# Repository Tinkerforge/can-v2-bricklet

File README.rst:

CAN Bricklet 2.0
================

This repository contains the firmware source code and the hardware design
files. The documentation generator configs can be found at
https://github.com/Tinkerforge/generators

Repository Content
------------------

software/:
 * examples/: Examples for all supported languages
 * build/: Compiled files
 * src/: Source code of firmware
 * Makefile: Makefile to build project

hardware/:
 * Contains KiCad project files and additionally schematics as PDF

datasheets/:
 * Contains datasheets for sensors and complex ICs that are used

Hardware
--------

The hardware is designed with the open source EDA Suite KiCad
(http://www.kicad.org). Before you are able to open the files,
you have to install the Tinkerforge kicad-libraries
(https://github.com/Tinkerforge/kicad-libraries). You can either clone
them directly in hardware/ or clone them in a separate folder and
symlink them into hardware/
(ln -s kicad_path/kicad-libraries project_path/hardware). After that you
can open the .pro file in hardware/ with KiCad and from there view and
modify the schematics and the PCB layout.

Software
--------

If you want to do your own Brick/Bricklet firmware development we highly
recommend that you use our build environment setup script and read the
tutorial (https://www.tinkerforge.com/en/doc/Tutorials/Tutorial_Build_Environment/Tutorial.html).

To compile the C code we recommend you to install the newest GNU Arm Embedded
Toolchain (https://launchpad.net/gcc-arm-embedded/+download).
You also need to install bricklib2 (https://github.com/Tinkerforge/bricklib2).

You can either clone it directly in software/src/ or clone it in a
separate folder and symlink it into software/src/
(ln -s bricklib_path/bricklib2 project_path/software/src/). Finally make sure to
have CMake installed (http://www.cmake.org/cmake/resources/software.html).

After that you can build the firmware by invoking make in software/.
The firmware (.zbin) can then be found in software/build/ and uploaded
with brickv (click button "Flashing" on start screen).

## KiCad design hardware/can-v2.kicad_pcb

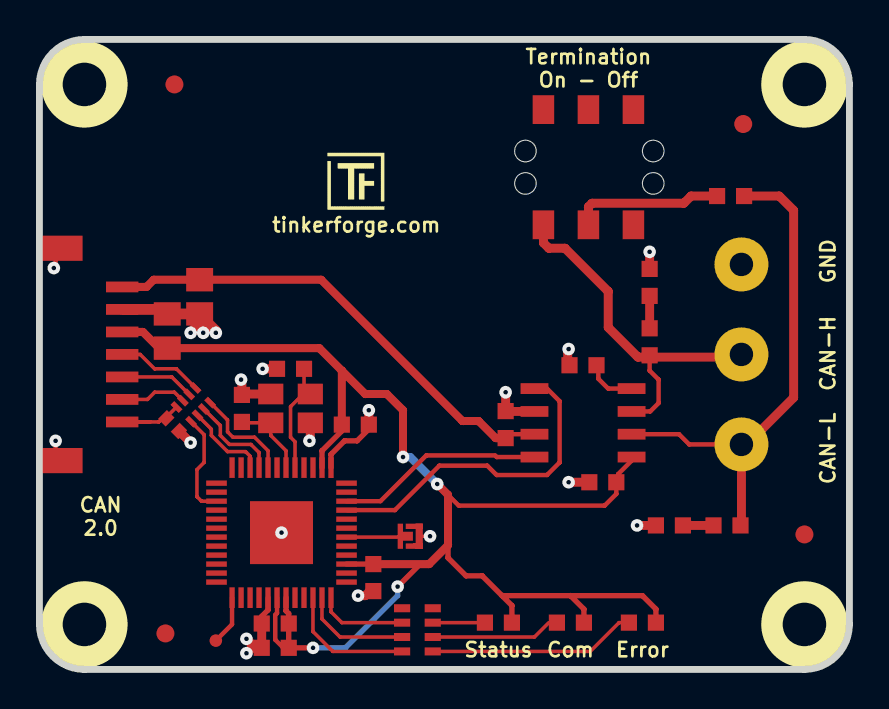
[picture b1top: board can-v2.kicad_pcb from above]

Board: 2 copper layers, 45.0 x 35.0 mm, 40 parts (0 on the bottom side), 29 nets.

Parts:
C1: 220pF; C0402F
C2, C3: 10uF; C0805E
C6, C7: 10pF; C0603F
C8, C9, C10, C12, C13: 100nF; C0603F
C11: 220nF; C0603F
C14, C15: 470pF; C0603F
D1: blue; D0603F
D2: yellow; D0603F
D3: red; D0603F
Fiducial_Mark: VAL**; Fiducial_Mark
Fiducial_Mark#2, Fiducial_Mark#3, Fiducial_Mark#4: VAL**; Fiducial_Mark
K1: CONN_3; AKL_5_3
P1: CON-SENSOR; CON-SENSOR2
P2: Debug; DEBUG_PAD
P3: Boot; SolderJumper
R2: 1k; R0603F
R3, R4, R5: 120; R0603F
RP1: 82; 4X0402
RP2: 1k; 0603X4
SW1: Termination; SLIDE_SWITCH
U1: XMC1404; QFN48-EP2
U2: MCP2562; SOIC8
U3, U4, U5, U6: DRILL; DRILL_NP
VAL: WEEE_7mm
VAL#2: CE_5mm
X1: 16MHz; CRYSTAL_3225

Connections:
3V3: C3.2, C8.2, C9.2, C10.2, C11.2, C12.1, D1.1, D2.1, D3.1, P1.3, U1.18, U1.19, U1.27, U1.38, U2.5
+5V: C2.2, C13.1, P1.1, U2.3
GND: C1.1, C2.1, C3.1, C6.2, C7.2, C8.1, C9.1, C10.1, C11.1, C12.2, C13.2, C14.2, C15.2, K1.1, P1.2, P1.EP, P3.1, R2.1, U1.17, U1.37, U1.EP, U2.2, X1.3
unnamed: C1.2, P1.7, RP1.4
unnamed: C6.1, U1.41, X1.1
unnamed: C7.1, U1.42, X1.2
unnamed: C14.1, R3.1
unnamed: C15.1, R4.1
unnamed: D1.2, RP2.7
unnamed: D2.2, RP2.6
unnamed: D3.2, RP2.5
unnamed: K1.2, R4.2, SW1.1, U2.7
unnamed: K1.3, R3.2, R5.1, U2.6
unnamed: P1.4, RP1.1
unnamed: P1.5, RP1.2
unnamed: P1.6, RP1.3
unnamed: P2.1, U1.13
unnamed: P3.2, U1.30
unnamed: R2.2, U2.8
unnamed: R5.2, SW1.2
unnamed: RP2.2, U1.24
unnamed: RP2.3, U1.23
unnamed: RP2.4, U1.22
RX: U1.34, U2.4
S-CLK: RP1.7, U1.45
S-CS: RP1.8, U1.44
S-MISO: RP1.5, U1.3
S-MOSI: RP1.6, U1.46
TX: U1.33, U2.1

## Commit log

2018-01-15 add readme
2018-01-16 add prototype hardware
2018-01-19 change text orientation
2018-02-20 Add .gitignore
2018-02-20 Cleanup KiCad libraries config
    Ensure LibDir=kicad-libraries and LibName1=tinkerforge.
    Remove special library.
2018-03-02 Add initial firmware
    That every seconds sends a dummy data frame.
2018-03-06 Add TX hardware FIFO logic
    Just transmits dummy data for now.
2018-03-06 Add MultiCAN+ datasheet
2018-03-07 Add TX buffer and feed TX FIFO from it
2018-03-07 Add custom MO helpers to avoid quirks and memory overhead in the XMC library
2018-03-07 Add RX FIFO and buffer
2018-03-08 Add basic config for extra LEDs
2018-03-08 Add simple read/write tests
2018-03-08 Rename buffer to backlog
2018-03-08 Unify count/size to size
2018-03-08 Extend write-frame to handle remote frames
2018-03-08 Split RX FIFO into multiple RX FIFOs
    To allow reception of data and remote frames along with the ability
    to have multiple acceptance filters, one per RX FIFO.
2018-03-08 Convert write/read-frame functions to streaming
2018-03-08 Add custom baudrate to bit-timing calculation
    The XMC library function for this doesn't take the DIV8 option into
    account and therefore cannot handle baudrates below 100 kbps.
2018-03-09 Fix TSEG1 range
2018-03-09 Add loopback mode using the second CAN node
2018-03-09 Fix typo in comment
2018-03-09 Whitespace
2018-03-12 Add write-buffer-timeout
2018-03-12 Add extra MO type to use last backlog slots
2018-03-12 Use frame-counter to read RF FIFOs in frame reception order
2018-03-12 Cleanup MO/buffer naming
2018-03-13 Update API
2018-03-13 Add frame-read callback
2018-03-13 Add get/set-tranceiver-configuration logic
2018-03-14 Remove unnecessary intermediate config variables
2018-03-14 Add queue and read filter configuration
2018-03-14 Add read-only mode
2018-03-14 Add communication and error LED config
2018-03-15 fix led text
2018-03-15 fix text, change logo orientation
2018-03-15 Properly handle disabled TX/RX backlogs
2018-03-15 Add error counters
2018-03-15 Reconfigure queues when entering/leaving loopback mode
    Otherwise the RX queue ends up being on the wrong CAN node, because in
    loopback the second CAN node is used for reception, but in non-loopback
    mode the first CAN node is used for transmission and reception.
2018-03-15 Don't set RXEN on RX FIFO slave objects
    This is not necessary for proper RX FIFO operation and it results in
    possible reception of frames in the middle of the RX FIFO because
    RX FIFO slave objects are normal message objects that take part in
    the acceptance filtering process if RXEN is set.
    This is especially noticable when using a read filter, because then
    frames that would be rejected by the read filter are recevied into
2018-03-15 Rename some error related things
2018-03-16 Properly recover from bus-off state
2018-03-27 specify processor
2018-04-23 Add 3d information (final)
2018-04-23 Add 3d model (*.FCStd & *.step)
2018-05-04 Rename files
2018-05-04 Add schematic PDF
2018-05-30 Add sample-point config option
2018-05-30 Add example skeletons
2018-05-30 Fix examples
2018-06-04 Disable debug
2018-06-05 examples: Fix write-frame call
2018-06-05 examples: Avoid temporary variables if possible
2018-06-05 Correctly set DIV8 config bit
2018-06-05 Add LabVIEW example
2018-06-07 Update changelog for initial release
2018-06-08 fix termination text
2018-06-18 Change capacitor footprint(s) to C0402F
2018-06-28 Fix readme
2018-07-11 Add Makefile with docker support
2018-07-11 Remove obsolete generate_makefile scripts
2018-07-11 Update directory structure and build instructions
2018-07-17 examples: Pass data as anonymous array
2018-10-04 Increase version for new release (changes in bricklib2)
2018-10-04 Add rev to changelog
2018-11-06 Add rust examples
2018-11-07 rust: Accept host names for ip connection, fix naming inconsistencies
2018-11-07 rust: Rename callback receivers.
2018-12-14 Add go examples.
2018-12-18 go: Change import path.
2018-12-18 go: Change import path again.
2018-12-20 rust: Reformat examples.
2019-01-24 mqtt: Add examples.
2019-01-24 mqtt: Remove executable bit in example permissions.
2019-01-24 go: Minor example fixes.
2019-08-22 c: Adapt to bindings changes
2019-10-04 Add initial support for timestamped frame handling
2019-11-13 Add datasheets
2020-01-14 examples: Use python3 input by default.
2020-02-26 Disable incomplete timestamped frame functions for now.
2020-02-27 Add frame readable callback.
2020-02-27 Fix disabled callback list.
2020-02-27 Mark error counters used in interrupt volatile.
2020-02-27 Add error occured callback.
2020-02-28 Fix typo.
2020-02-28 Append to changelog.
2020-02-28 Add commit ref to changelog.
2020-02-28 Fix bit0 error handling in bus-off mode
2020-02-28 Add commit ref to changelog
2020-03-16 rust: Update to new skeleton
2020-03-17 examples: Add constant translation for frame type
2020-03-17 mqtt: Fix syntax error
2020-03-17 matlab: Fix format strings
2020-03-17 vbnet: Use common style
2020-04-03 Add openHAB examples.
2020-08-19 Add uc examples.
2020-08-25 uc: Adapt example to new skeleton
2020-08-27 uc: Fix warnings.
2020-08-31 uc: Use fixed-with placeholders in format strings.
2020-09-02 uc: Add example driver note.
2020-10-27 perl: Fix syntax error
2021-05-27 php: Remove incomplete marker
2021-10-25 Update KiCad link
    https://www.kicad.org/blog/2021/10/Avoid-links-to-former-kicad-domain/
2022-04-19 examples: uc: Rename TF_HalContext to TF_HAL.
2022-04-26 uc: Adapt to bindings changes
2022-07-06 Add license files.
2022-11-09 labview: Fix SetTransceiverConfigurarion call
2022-11-10 labview: Add separate read and write examples
2022-11-14 labview: Add example for frame-read function
2025-10-04 Fix compatibility with new Docker build image (GCC 14.2.1)

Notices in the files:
hardware/can-v2.kicad_pcb:
Licensed under CERN OHL v.1.1
Copyright (©) 2018, B.Nordmeyer
Copyright Tinkerforge GmbH 2018.
This documentation describes Open Hardware and is licensed under the
CERN OHL v. 1.1.
